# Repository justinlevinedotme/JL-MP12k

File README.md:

# JL-MP12k

A macropad featuring 12 keys, an OLED, and rotary encoder.

More documentation to come, this is mostly for my own reference.

[View on KiCanvas](https://kicanvas.org/?github=https%3A%2F%2Fgithub.com%2Fjustinlevinedotme%2FJL-MP12k)

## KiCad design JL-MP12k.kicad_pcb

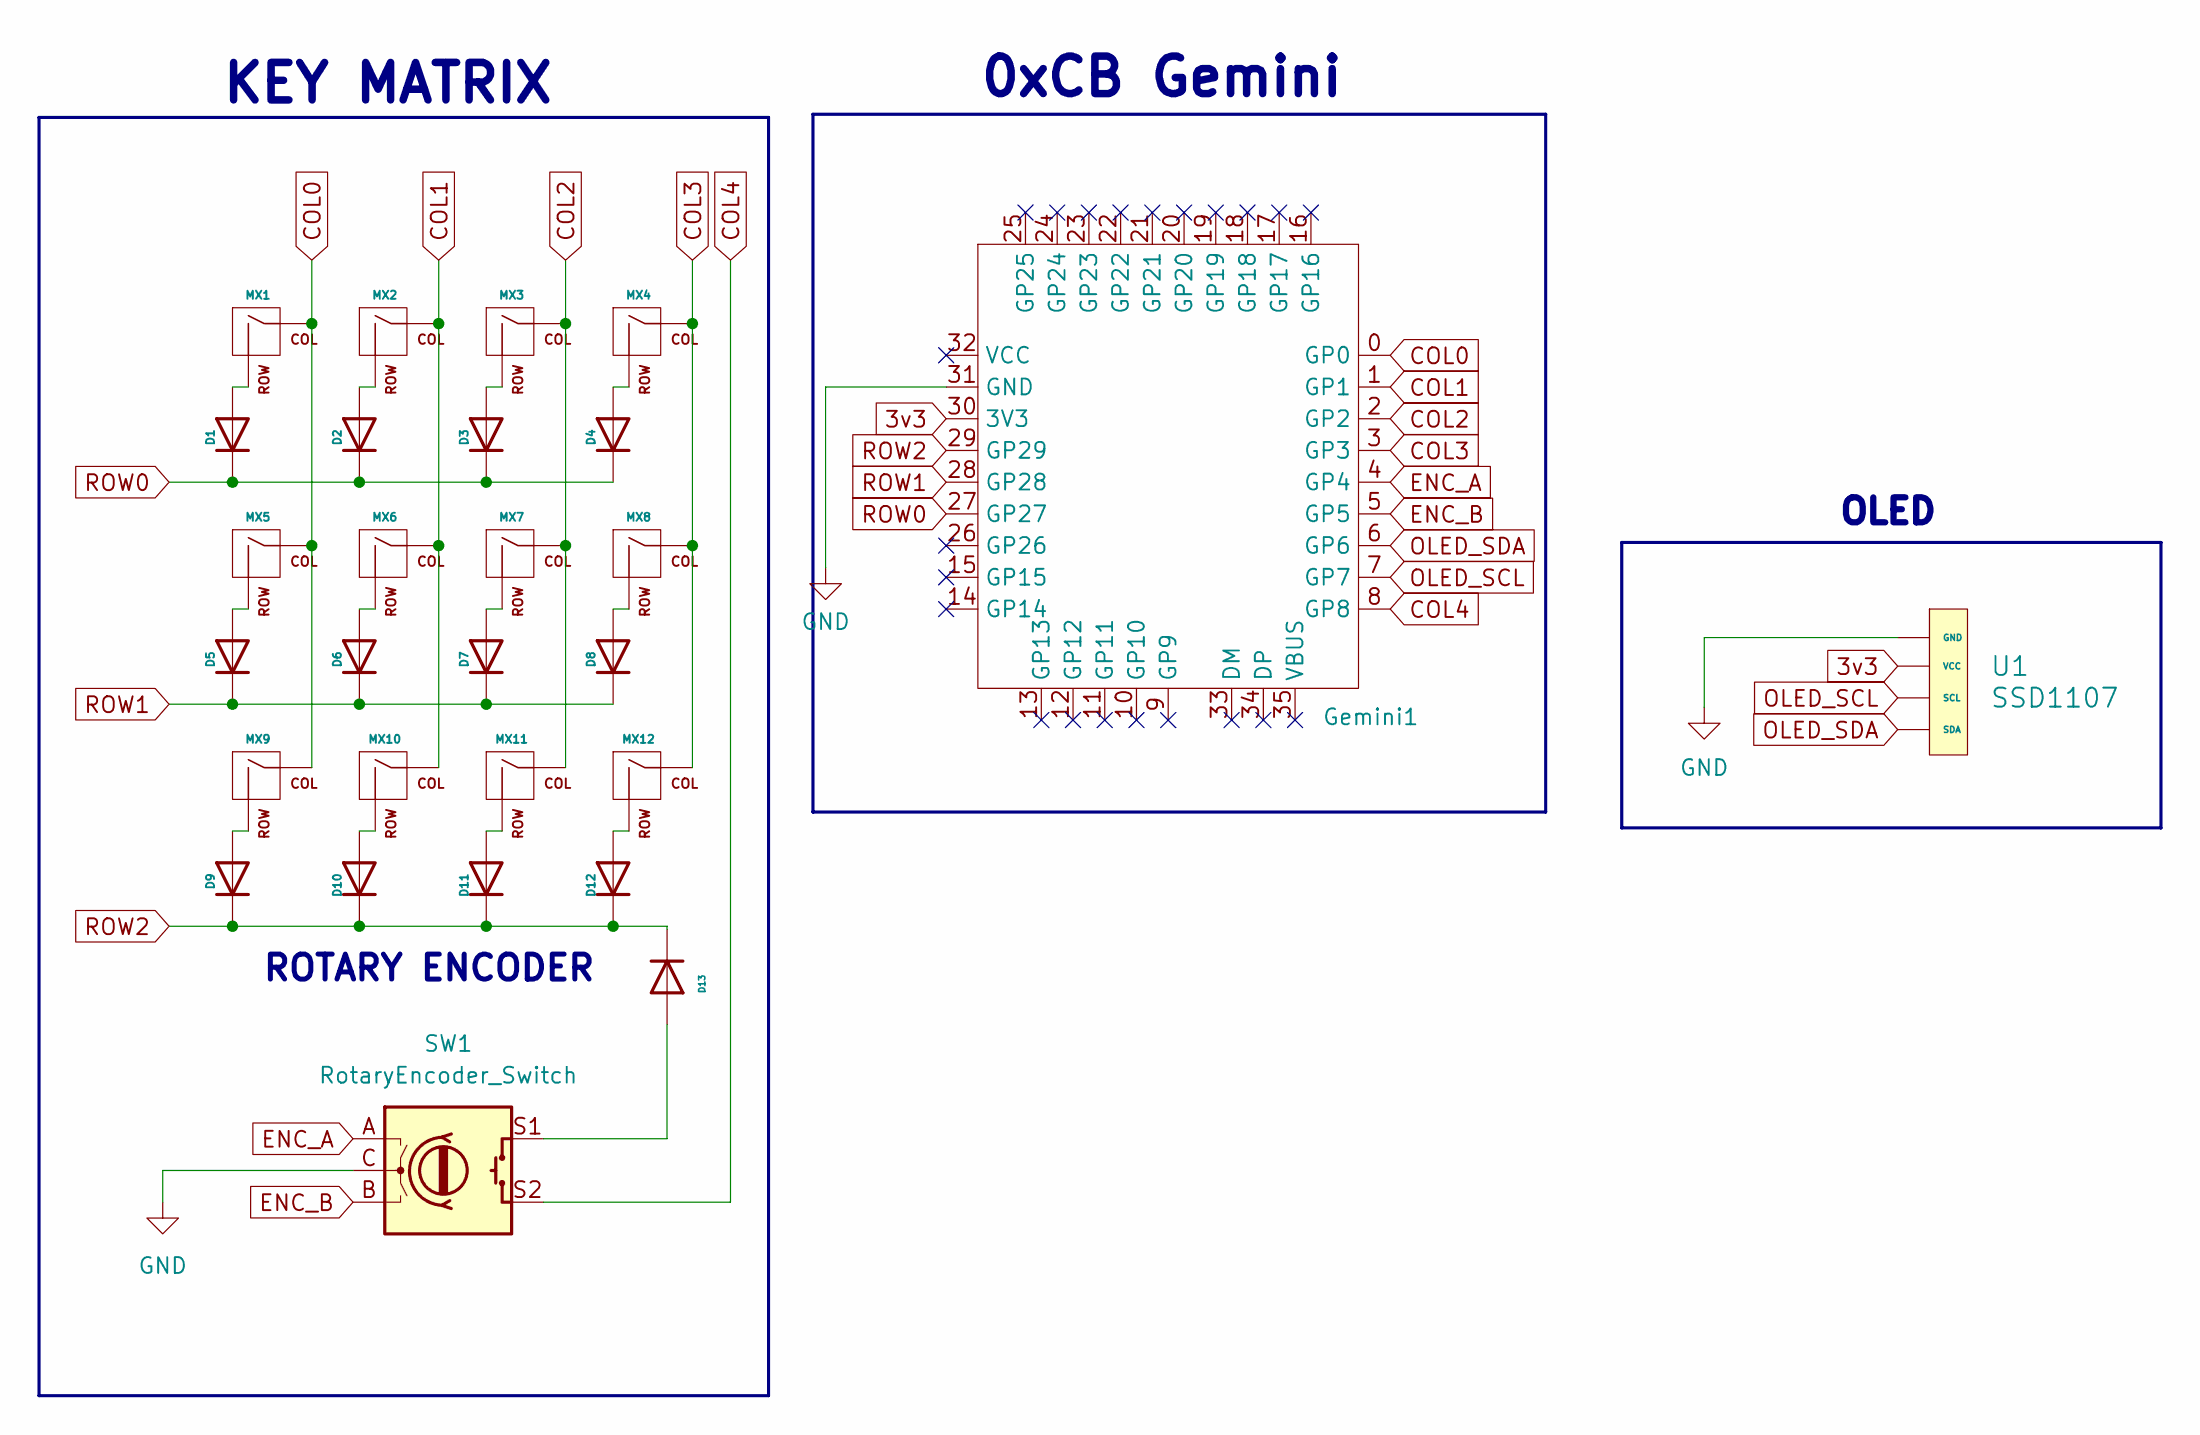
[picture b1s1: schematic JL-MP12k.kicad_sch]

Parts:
D1: 1N4148W; D_SOD-123_ALT; LCSC Part # C77978
D2, D3, D4, D5, D6, D7, D8, D9, D10, D11, D12: 1N4148W; D_SOD-123_ALT; LCSC C77978
D13: 1N4148W; D_SOD-123
Gemini1: 0xCB Gemini
MX1: MX-NoLED; SW_Hotswap_Kailh_MX; LCSC C2803348
MX2, MX3, MX4, MX5, MX6, MX7, MX8, MX9, MX10, MX11, MX12: MX-NoLED; SW_Hotswap_Kailh_MX; JLCPCB Part # C2803348
SW1: RotaryEncoder_Switch; RotaryEncoder_Alps_EC11E-Switch_Vertical_H20mm; LCSC Part # C361165
U1: SSD1107; OLED 4PIN 64×128 SSD1107

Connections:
3v3: Gemini1.30 (3V3), U1.2 (VCC)
COL0: Gemini1.0 (GP0), MX1.1 (COL), MX5.1 (COL), MX9.1 (COL)
COL1: Gemini1.1 (GP1), MX2.1 (COL), MX6.1 (COL), MX10.1 (COL)
COL2: Gemini1.2 (GP2), MX3.1 (COL), MX7.1 (COL), MX11.1 (COL)
COL3: Gemini1.3 (GP3), MX4.1 (COL), MX8.1 (COL), MX12.1 (COL)
COL4: Gemini1.8 (GP8), SW1.S2
ENC_A: Gemini1.4 (GP4), SW1.A
ENC_B: Gemini1.5 (GP5), SW1.B
GND: Gemini1.31 (GND), SW1.C, U1.1 (GND)
unnamed: D1.2 (A), MX1.2 (ROW)
unnamed: D2.2 (A), MX2.2 (ROW)
unnamed: D3.2 (A), MX3.2 (ROW)
unnamed: D4.2 (A), MX4.2 (ROW)
unnamed: D5.2 (A), MX5.2 (ROW)
unnamed: D6.2 (A), MX6.2 (ROW)
unnamed: D7.2 (A), MX7.2 (ROW)
unnamed: D8.2 (A), MX8.2 (ROW)
unnamed: D9.2 (A), MX9.2 (ROW)
unnamed: D10.2 (A), MX10.2 (ROW)
unnamed: D11.2 (A), MX11.2 (ROW)
unnamed: D12.2 (A), MX12.2 (ROW)
unnamed: D13.2 (A), SW1.S1
OLED_SCL: Gemini1.7 (GP7), U1.3 (SCL)
OLED_SDA: Gemini1.6 (GP6), U1.4 (SDA)
ROW0: D1.1 (K), D2.1 (K), D3.1 (K), D4.1 (K), Gemini1.27 (GP27)
ROW1: D5.1 (K), D6.1 (K), D7.1 (K), D8.1 (K), Gemini1.28 (GP28)
ROW2: D9.1 (K), D10.1 (K), D11.1 (K), D12.1 (K), D13.1 (K), Gemini1.29 (GP29)

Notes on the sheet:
OLED
0xCB Gemini
KEY MATRIX
ROTARY ENCODER

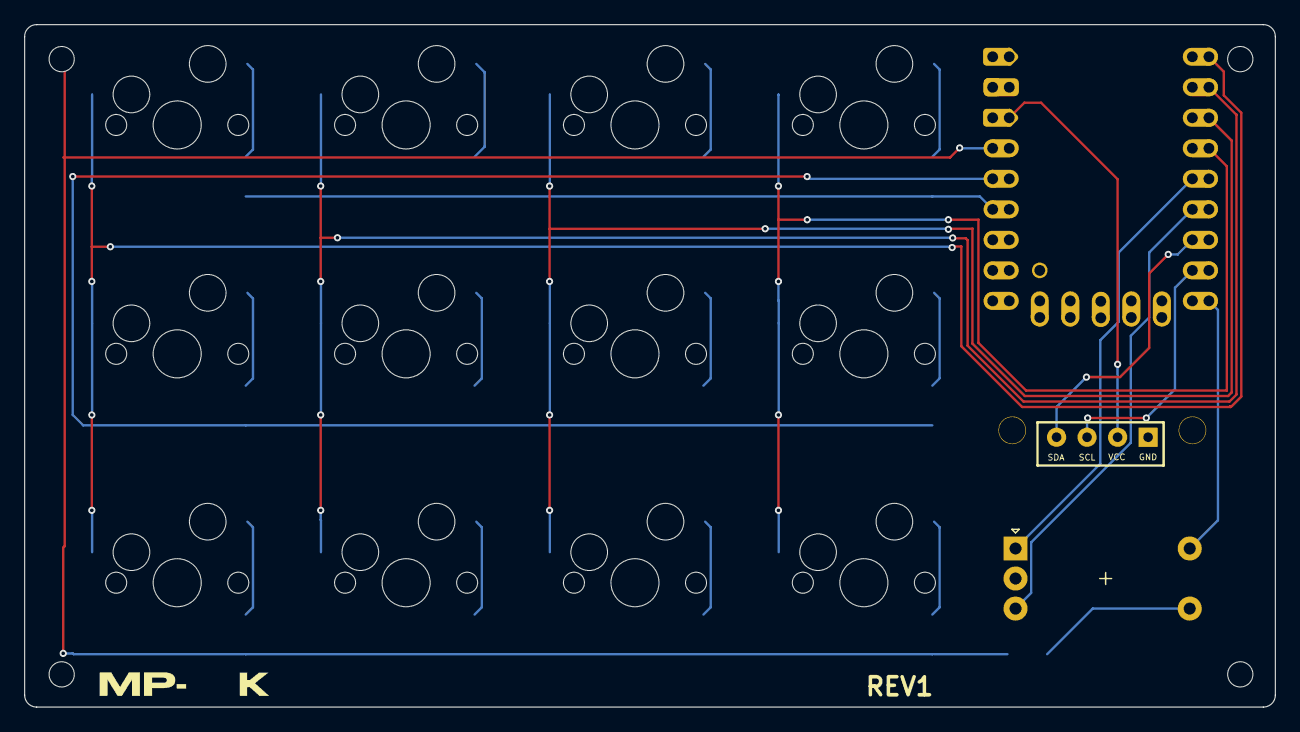
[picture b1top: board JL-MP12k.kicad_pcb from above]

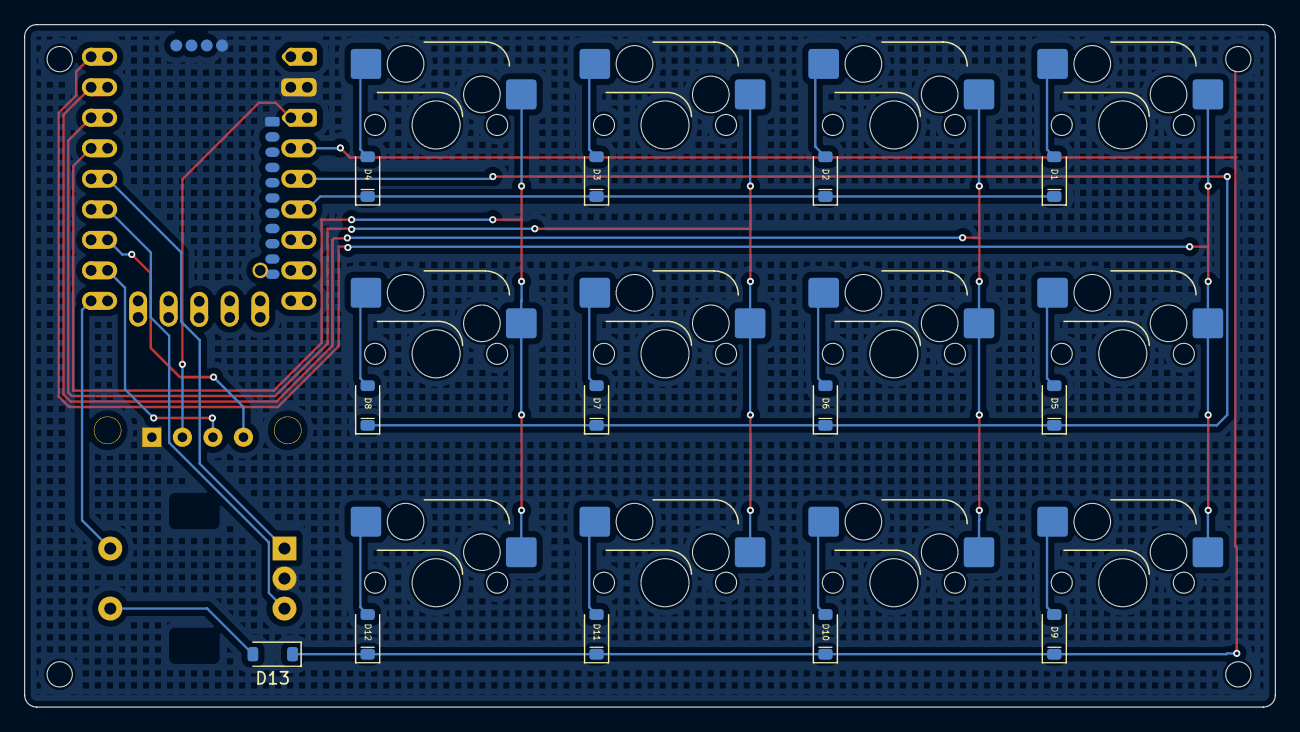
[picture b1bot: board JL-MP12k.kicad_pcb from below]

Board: 2 copper layers, 104.1 x 56.8 mm, 28 parts (13 on the bottom side), 27 nets.

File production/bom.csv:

Designator,Footprint,Quantity,Value,LCSC Part #
"D1, D10, D11, D12, D2, D3, D4, D5, D6, D7, D8, D9",D_SOD-123_ALT,12,1N4148W,C77978
"MX1, MX10, MX11, MX12, MX2, MX3, MX4, MX5, MX6, MX7, MX8, MX9",SW_Hotswap_Kailh_MX,12,MX-NoLED,
SW1,RotaryEncoder_Alps_EC11E-Switch_Vertical_H20mm,1,RotaryEncoder_Switch,C361165
U1,OLED 4PIN 64×128 SSD1107,1,SSD1107,

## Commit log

2025-09-02 JL-MP12k Initial Commit
2025-09-02 Add production files and update PCB settings
    Added new production outputs including BOM, designators, netlist, and positions CSVs, as well as backup and schematic/assembly images. Updated KiCad project files to adjust drill shape, output direct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
2025-09-02 fixed some stuff
    rev 1.1
